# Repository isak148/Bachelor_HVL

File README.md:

# TODO liste
- Sette opp test program for sesnsorer. 
- Sette teste sensorene.
- Begynne å lage et skjema for kode struktur.
- Sette opp klasser og funksjoner.
- Lage lese/skrive til fil program.

# Handleliste
- pulsbelte
- spacers til raspberry 1-cm
- hdmi - micor hdmi
-

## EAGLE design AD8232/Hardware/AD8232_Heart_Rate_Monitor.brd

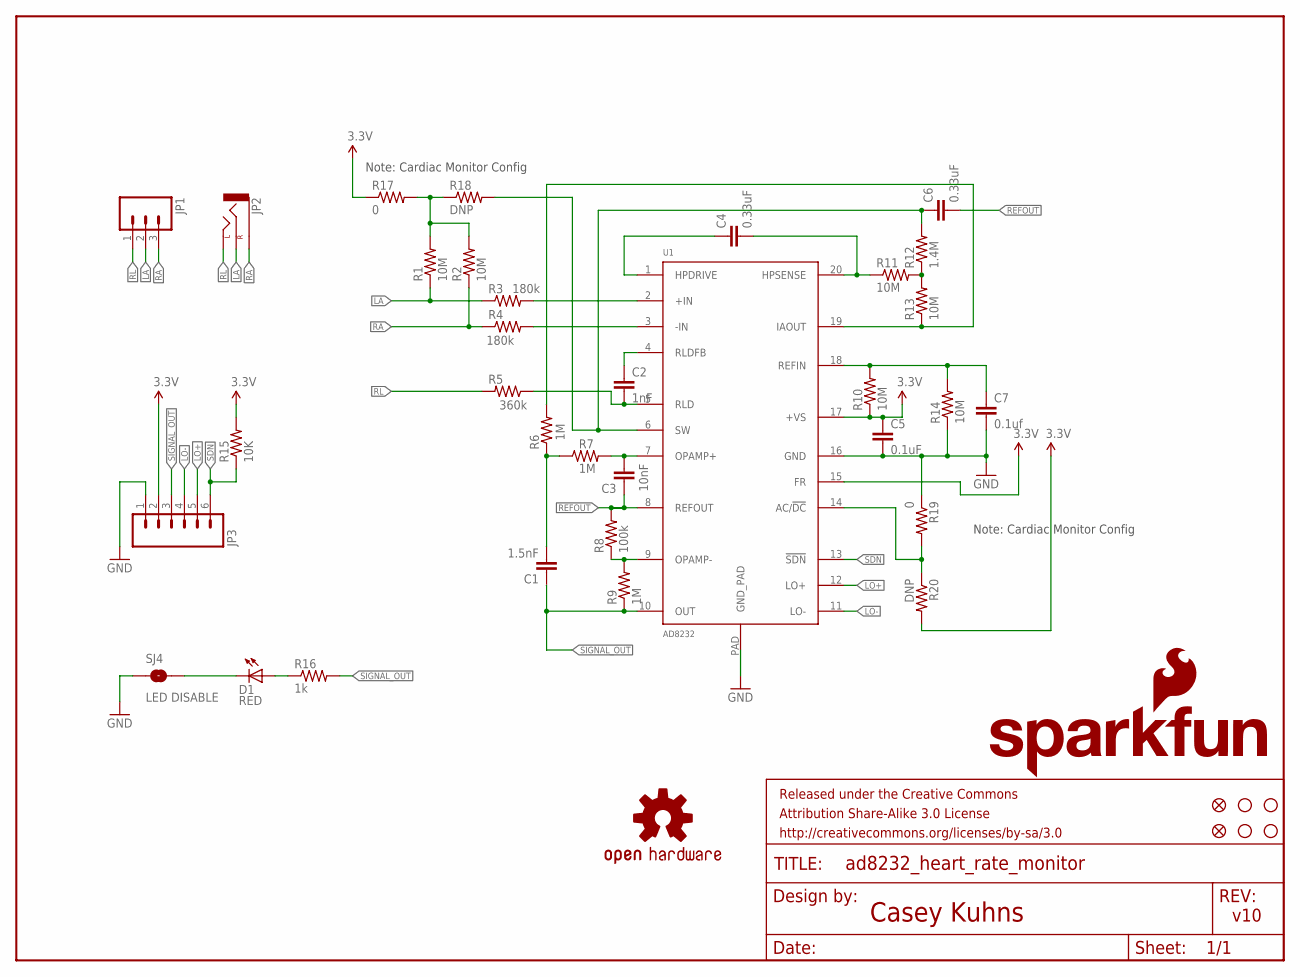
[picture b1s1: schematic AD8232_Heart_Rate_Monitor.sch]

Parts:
C1: 1.5nF; 0603-CAP
C2: 1nF; 0603-CAP
C3: 10nF; 0603-CAP
C4, C6: 0.33uF; 0805
C5: 0.1uF; 0603-CAP
C7: 0.1uf; 0603-CAP
D1: RED; LED-0603
FID1, FID2: FIDUCIAL1X2; FIDUCIAL-1X2
FRAME1: FRAME-LETTER; CREATIVE_COMMONS
JP1: M03PTH; 1X03
JP2: AUDIO-JACKSMD2; AUDIO-JACK-3.5MM-SMD
JP3: M06SIP; 1X06
LOGO1: OSHW-LOGOS; OSHW-LOGO-S
LOGO2: SFE_LOGO_NAME_FLAME.1_INCH; SFE_LOGO_NAME_FLAME_.1
R1, R2, R10, R11, R13, R14: 10M; 0603-RES
R3, R4: 180k; 0603-RES
R5: 360k; 0603-RES
R6, R7, R9: 1M; 0603-RES
R8: 100k; 0603-RES
R12: 1.4M; 0603-RES
R15: 10K; 0603-RES
R16: 1k; 0603-RES
R17, R19: 0; 0603
R18, R20: DNP; 0603
SJ4: LED DISABLE; SJ_2S-TRACE
STANDOFF1, STANDOFF2, STANDOFF3, STANDOFF4: STAND-OFF
U1: AD8232; LFCSP_20

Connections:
3.3V: C5.1, JP3.2, R10.1, R15.2, R17.1, R20.2, U1.15 (FR), U1.17 (+VS)
GND: C5.2, C7.2, JP3.1, R14.1, R19.1, SJ4.1, U1.16 (GND), U1.PAD (GND_PAD)
LA: JP1.2, JP2.RING (RIGHT), R1.1, R3.1
LO+: JP3.5, U1.12 (LO+)
LO-: JP3.4, U1.11 (LO-)
unnamed: R3.2, U1.2 (+IN)
unnamed: R4.2, U1.3 (-IN)
unnamed: C3.2, R7.2, U1.7 (OPAMP+)
unnamed: C4.2, R11.1, U1.20 (HPSENSE)
unnamed: C7.1, R10.2, R14.2, U1.18 (REFIN)
unnamed: D1.A, R16.1
unnamed: R8.1, R9.2, U1.9 (OPAMP-)
unnamed: R6.2, R13.1, U1.19 (IAOUT)
unnamed: C1.2, R6.1, R7.1
unnamed: D1.C, SJ4.2
unnamed: R19.2, R20.1, U1.14 (AC/!DC)
unnamed: C4.1, U1.1 (HPDRIVE)
unnamed: R11.2, R12.1, R13.2
unnamed: C6.1, R12.2, R18.2, U1.6 (SW)
unnamed: C2.1, U1.4 (RLDFB)
unnamed: C2.2, R5.1, U1.5 (RLD)
unnamed: R1.2, R2.2, R17.2, R18.1
RA: JP1.3, JP2.SLEEVE, R2.1, R4.1
REFOUT: C3.1, C6.2, R8.2, U1.8 (REFOUT)
RL: JP1.1, JP2.TIP (LEFT), R5.2
SDN: JP3.6, R15.1, U1.13 (!SDN)
SIGNAL_OUT: C1.1, JP3.3, R9.1, R16.2, U1.10 (OUT)

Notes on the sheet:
Casey Kuhns
v10
Note: Cardiac Monitor Config

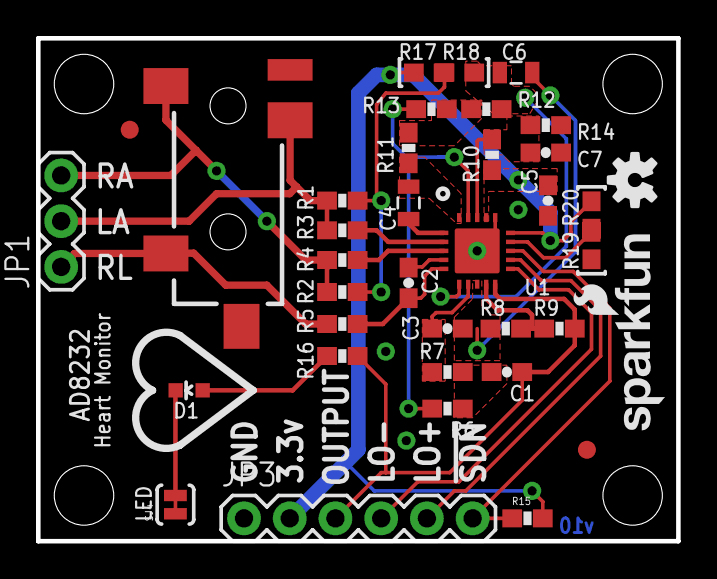
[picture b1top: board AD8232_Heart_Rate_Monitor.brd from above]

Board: 2 copper layers, 35.6 x 27.9 mm, 42 parts (0 on the bottom side), 27 nets.

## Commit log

2025-02-24 test
2025-02-24 pakker og prgrammer til sensorer
2025-02-24 heart rate monitor
2025-02-24 ToDo liste
2025-02-25 Oppdatert to do
2025-02-25 Test program for MPU og MS(ufullstendig)
2025-02-26 ny AD8232 +
2025-02-26 fjernet llog
2025-02-26 opp ryding
2025-03-04 tore fix
2025-03-04 Fungerende senorer
2025-03-04 data fra arduino
2025-03-06 kalibrering av mpu
2025-03-07 små ting
2025-03-07 filbehandling
2025-03-07 sensor data
2025-03-07 formatering
2025-03-07 ny test
2025-03-07 sensordata vl6180x
2025-03-07 sensordata_vl6180x
2025-03-07 graf ploting
2025-03-07 opdate
2025-03-07 fil lagring ms5837
2025-03-07 ferdig data
2025-03-07 data ms5837
2025-03-07 samlet kode
2025-03-07 therding
2025-03-07 therding2
2025-03-07 commit: threding
2025-03-07 datapunkt
2025-03-07 upadter
2025-03-07 oppstart
2025-03-10 data analyse
2025-03-12 ad up
2025-03-12 adup
2025-03-12 adupu
2025-03-12 ad1015
2025-03-12 data
2025-03-19 OPPDATERING TIL SAMLET KODE
2025-03-19 små endringer
2025-03-26 aktivitetgjennkjenning
2025-03-26 akselerasjon
2025-03-28 opdatert puls
2025-03-28 oppdatering
2025-03-31 data1
2025-03-31 nytt script
2025-03-31 oppdatert
2025-03-31 Update puls_bachelor_test2
2025-04-01 noe som ikkje fungerer
2025-04-01 name change
2025-04-01 Kalman til mpu6050
2025-04-01 kalman
2025-04-01 orginal
2025-04-01 endring
2025-04-01 endringer
2025-04-01 Mahony
2025-04-01 nyttt forsøk
2025-04-01 github
2025-04-01 fjerner unødvenig
2025-04-01 push
2025-04-01 boss
2025-04-01 test100000
2025-04-02 uodate
2025-04-02 nååå
2025-04-03 data bachelor_test4
2025-04-03 upda
2025-04-03 tada
2025-04-03 opdatert
2025-04-03 shit
2025-04-07 backup
2025-04-07 backup_update
2025-04-08 send
2025-04-08 next
2025-04-08 downgrade
2025-04-08 down
2025-04-09 nytt forsøk
2025-04-09 sjekk
2025-04-09 dgfsgsf
2025-04-09 test nr 1
2025-04-10 strukturering
2025-05-09 flanke
2025-05-12 this works
2025-05-18 Lagring
2025-05-18 test 1
2025-05-18 test 1 + 2
2025-05-18 up time sleep
2025-05-18 test 3
2025-05-19 retting
2025-05-20 rydding

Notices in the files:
parts and their libraries:
SparkFun-Aesthetics: Licensing: CC v3.0 Share-Alike You are welcome to use this library for commercial purposes.
SparkFun-Aesthetics: Released under the Creative Commons Attribution Share-Alike 3.0 License
SparkFun-Aesthetics: http://creativecommons.org/licenses/by-sa/3.0
